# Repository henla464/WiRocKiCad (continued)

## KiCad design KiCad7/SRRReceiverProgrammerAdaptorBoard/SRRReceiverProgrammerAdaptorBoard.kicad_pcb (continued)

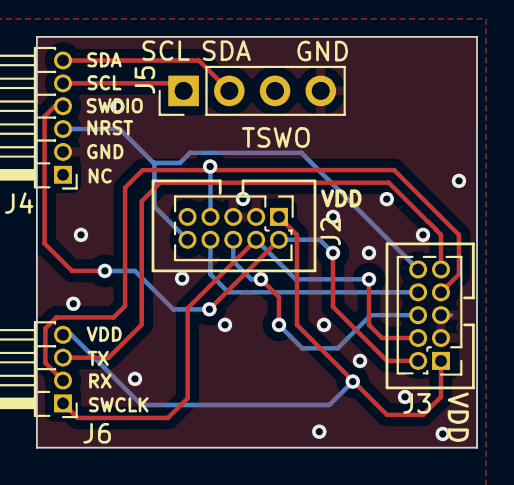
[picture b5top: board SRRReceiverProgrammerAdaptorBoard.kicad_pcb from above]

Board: 2 copper layers, 24.5 x 22.8 mm, 5 parts (0 on the bottom side), 11 nets.

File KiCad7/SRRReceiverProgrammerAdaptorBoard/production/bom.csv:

Designator,Footprint,Quantity,Value,LCSC Part #
"J2, J3",PinHeader_2x05_P1.27mm_Vertical,2,Conn_02x05_Odd_Even,
J4,PinHeader_1x06_P1.27mm_Horizontal,1,Conn_01x06,
J5,PinHeader_1x04_P2.54mm_Vertical,1,Conn_01x04,
J6,PinHeader_1x04_P1.27mm_Horizontal,1,Conn_01x04,
